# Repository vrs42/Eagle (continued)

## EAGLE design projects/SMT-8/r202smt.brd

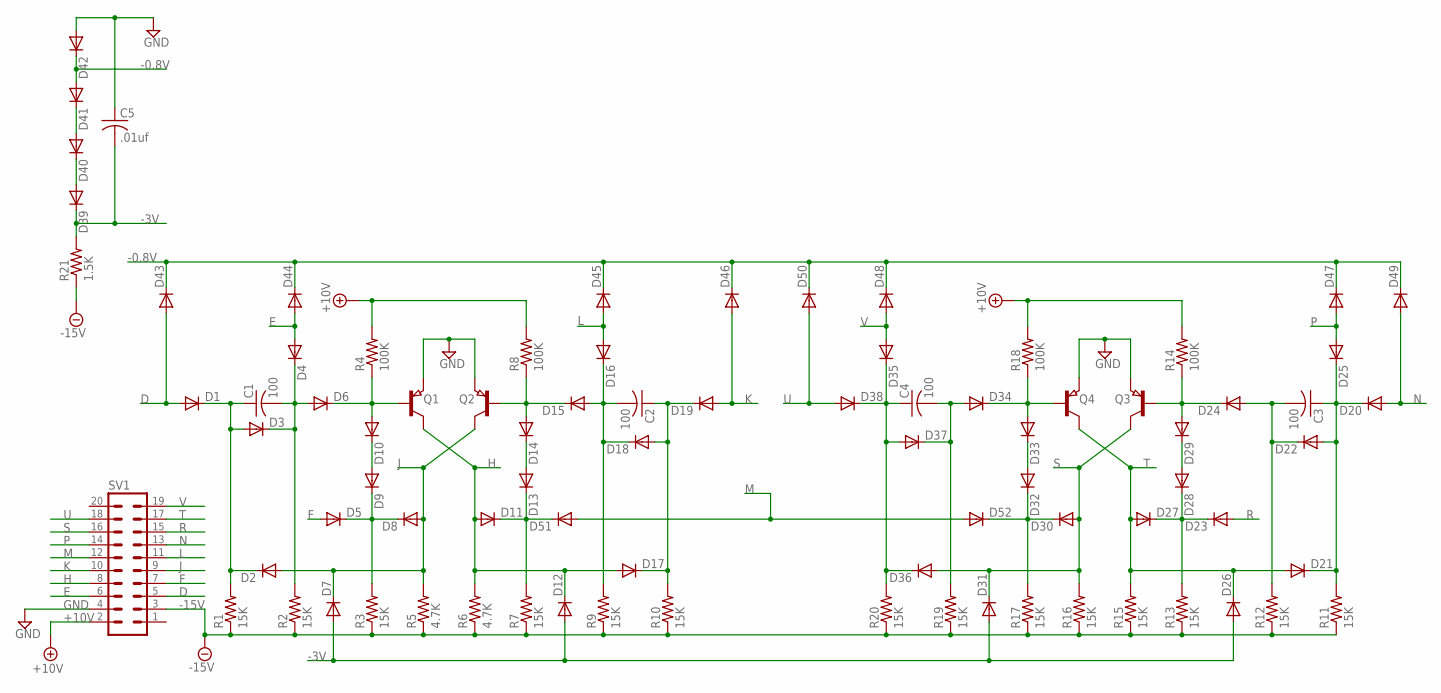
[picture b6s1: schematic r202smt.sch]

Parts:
C1, C2, C3, C4: 100; C0603
C5: .01uf; C1206
D1, D2, D3, D4, D5, D6, D7, D8, D9, D10, D11, D12, D13, D14, D15, D16, D17, D18, D19, D20, D21, D22, D23, D24, D25, D26, D27, D28, D29, D30, D31, D32, D33, D34, D35, D36, D37, D38, D39, D40, D41, D42, D43, D44, D45, D46, D47, D48, D49, D50, D51, D52: DIODE-SOD110-W; SOD110-W
Q1, Q2, Q3, Q4: PNP-TRANSISTOR_SOT23; SOT23
R1, R2, R3, R7, R9, R10, R11, R12, R13, R15, R16, R17, R19, R20: 15K; R0603
R4, R8, R14, R18: 100K; R0603
R5, R6: 4.7K; R0603
R21: 1.5K; R1206
SV1: MA10-2W

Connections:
+10V: R4.2, R8.2, R14.2, R18.2, SV1.2
-0.8V: D41.A, D42.C, D43.C, D44.C, D45.C, D46.C, D47.C, D48.C, D49.C, D50.C
-3V: C5.2, D7.A, D12.A, D26.A, D31.A, D39.C, R21.2
-15V: R1.1, R2.1, R3.1, R5.1, R6.1, R7.1, R9.1, R10.1, R11.1, R12.1, R13.1, R15.1, R16.1, R17.1, R19.1, R20.1, R21.1, SV1.3
D: D1.A, D43.A, SV1.5
E: D4.A, D44.A, SV1.6
F: D5.A, SV1.7
GND: C5.1, D42.A, Q1.2 (E), Q2.2 (E), Q3.2 (E), Q4.2 (E), SV1.4
H: D11.A, D12.C, D17.A, Q1.3 (C), R6.2, SV1.8
J: D2.A, D7.C, D8.A, Q2.3 (C), R5.2, SV1.9
K: D19.A, D46.A, SV1.10
L: D16.A, D45.A, SV1.11
M: D51.A, D52.A, SV1.12
N: D20.A, D49.A, SV1.13
unnamed: C1.1, D1.C, D2.C, D3.A, R1.2
unnamed: D14.A, D15.C, Q2.1 (B), R8.1
unnamed: C1.2, D3.C, D4.C, D6.A, R2.2
unnamed: C3.2, D22.C, D24.A, R12.2
unnamed: D6.C, D10.A, Q1.1 (B), R4.1
unnamed: D9.A, D10.C
unnamed: C3.1, D20.C, D21.C, D22.A, D25.C, R11.2
unnamed: D5.C, D8.C, D9.C, R3.2
unnamed: D11.C, D13.C, D51.C, R7.2
unnamed: C4.1, D35.C, D36.C, D37.A, D38.C, R20.2
unnamed: D13.A, D14.C
unnamed: C2.1, D17.C, D18.A, D19.C, R10.2
unnamed: C4.2, D34.A, D37.C, R19.2
unnamed: C2.2, D15.A, D16.C, D18.C, R9.2
unnamed: D33.A, D34.C, Q4.1 (B), R18.1
unnamed: D32.A, D33.C
unnamed: D30.C, D32.C, D52.C, R17.2
unnamed: D23.C, D27.C, D28.C, R13.2
unnamed: D24.C, D29.A, Q3.1 (B), R14.1
unnamed: D28.A, D29.C
unnamed: D39.A, D40.C
unnamed: D40.A, D41.C
P: D25.A, D47.A, SV1.14
R: D23.A, SV1.15
S: D30.A, D31.C, D36.A, Q3.3 (C), R16.2, SV1.16
T: D21.A, D26.C, D27.A, Q4.3 (C), R15.2, SV1.17
U: D38.A, D50.A, SV1.18
V: D35.A, D48.A, SV1.19

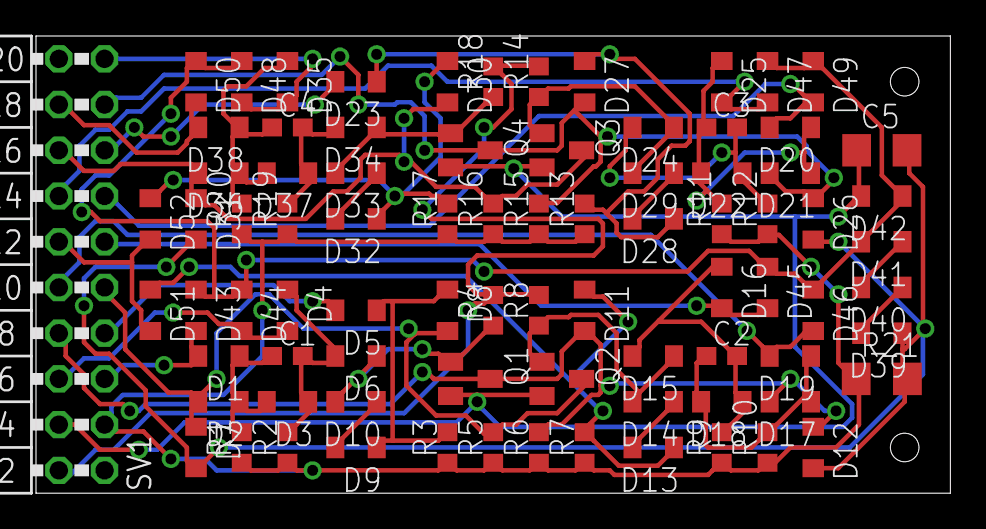
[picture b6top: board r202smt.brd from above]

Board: 2 copper layers, 50.8 x 25.4 mm, 83 parts (0 on the bottom side), 42 nets.
